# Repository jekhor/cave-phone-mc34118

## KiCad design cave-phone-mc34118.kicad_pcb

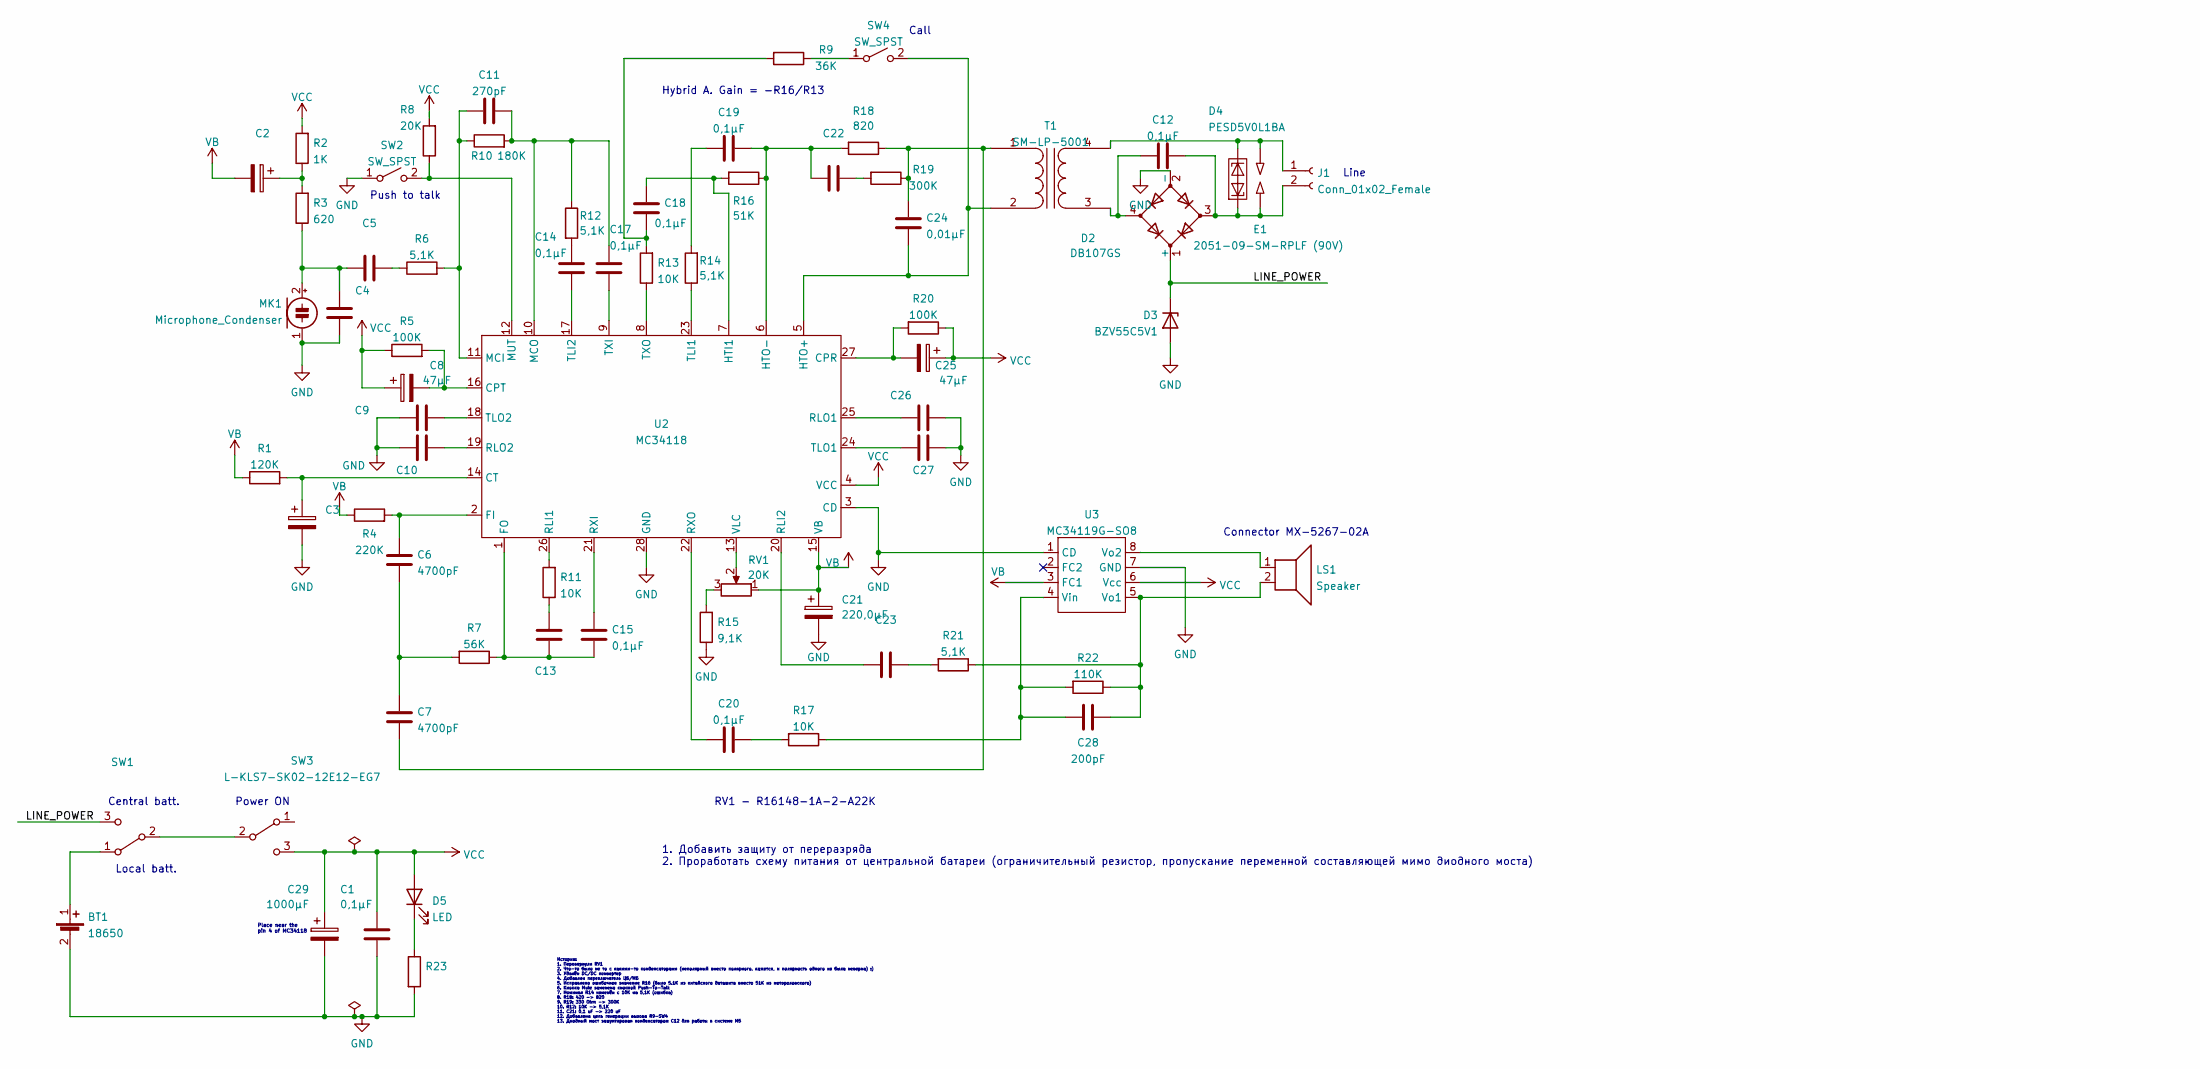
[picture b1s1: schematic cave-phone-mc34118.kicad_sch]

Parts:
BT1: 18650; BatteryHolder_MPD_BH-18650-PC2
C1, C12, C14, C15, C17, C18, C19, C20: 0,1µF; C_0805_2012Metric_Pad1.18x1.45mm_HandSolder
C2, C3: (no value)
C4, C5, C9, C10, C13, C22, C23, C26, C27: C_0805_2012Metric_Pad1.18x1.45mm_HandSolder
C6, C7: 4700pF; C_0805_2012Metric_Pad1.18x1.45mm_HandSolder
C8: 47µF; CP_EIA-3528-21_Kemet-B_Pad1.50x2.35mm_HandSolder
C11: 270pF; C_0805_2012Metric_Pad1.18x1.45mm_HandSolder
C21: 220,0µF
C24: 0,01µF; C_0805_2012Metric_Pad1.18x1.45mm_HandSolder
C25: 47µF
C28: 200pF; C_0805_2012Metric_Pad1.18x1.45mm_HandSolder
C29: 1000µF
D2: DB107GS; Diode_Bridge_Vishay_DFS
D3: BZV55C5V1; D_MiniMELF
D4: PESD5V0L1BA; D_SOD-323
D5: LED; LED_D3.0mm
E1: 2051-09-SM-RPLF (90V); Fuse_1812_4532Metric
J1: Conn_01x02_Female
LS1: Speaker; Molex_SPOX_5267-02A_1x02_P2.50mm_Vertical
MK1: Microphone_Condenser; MIC_CMA-4544PF-W
R1: 120K
R2: 1K
R3: 620
R4: 220K
R5, R20: 100K
R6, R12, R14, R21: 5,1K
R7: 56K
R8: 20K
R9: 36K
R10: 180K
R11, R13, R17: 10K
R15: 9,1K
R16: 51K
R18: 820
R19: 300K
R22: 110K
R23: (no value)
RV1: 20K; Potentiometer_Alps_RK163_Single_Horizontal
SW1: KLS7-SK02-12E12
SW2, SW4: SW_SPST
SW3: L-KLS7-SK02-12E12-EG7; KLS7-SK02-12E12
T1: SM-LP-5001
U2: MC34118; SOIC-28W_7.5x17.9mm_P1.27mm
U3: MC34119G-SO8; SOP-8_3.9x4.9mm_P1.27mm

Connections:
/LINE_POWER: D2.1 (+), D3.1 (K), SW1.3 (C)
GND: BT1.2 (-), C1.2, C3.2, C4.1, C9.1, C10.1, C21.2, C26.1, C27.1, C29.2, D2.2 (-), D3.2 (A), MK1.1 (-), R15.1, R23.2, SW2.1 (A), U2.3 (CD), U2.28 (GND), U3.1 (CD), U3.7 (GND)
unnamed: BT1.1 (+), SW1.1 (A)
unnamed: C2.1, R2.1, R3.2
unnamed: C3.1, R1.2, U2.14 (CT)
unnamed: C4.2, C5.1, MK1.2 (+), R3.1
unnamed: C5.2, R6.1
unnamed: C6.1, C7.2, R7.2
unnamed: C6.2, R4.2, U2.2 (FI)
unnamed: C8.2, R5.2, U2.16 (CPT)
unnamed: C9.2, U2.18 (TLO2)
unnamed: C10.2, U2.19 (RLO2)
unnamed: C11.1, C17.2, R10.2, R12.1, U2.10 (MCO)
unnamed: C11.2, R6.2, R10.1, U2.11 (MCI)
unnamed: C12.1, D2.3, D4.1 (K1), E1.1, J1.2
unnamed: C12.2, D2.4, T1.3 (SA)
unnamed: C13.1, C15.1, R7.1, U2.1 (FO)
unnamed: C13.2, R11.1
unnamed: C14.1, U2.17 (TLI2)
unnamed: C14.2, R12.2
unnamed: C15.2, U2.21 (RXI)
unnamed: C17.1, U2.9 (TXI)
unnamed: C18.1, R9.2, R13.2
unnamed: C18.2, R16.2, U2.7 (HTI1)
unnamed: C19.1, C22.2, R16.1, R18.2, U2.6 (HTO-)
unnamed: C19.2, R14.2
unnamed: C20.1, R17.2
unnamed: C20.2, U2.22 (RXO)
unnamed: C22.1, R19.2
unnamed: C23.1, R21.2
unnamed: C23.2, U2.20 (RLI2)
unnamed: C7.1, C24.1, R18.1, R19.1, T1.1 (AA)
unnamed: C24.2, SW4.2 (B), T1.2 (AB), U2.5 (HTO+)
unnamed: C25.2, R20.2, U2.27 (CPR)
unnamed: C26.2, U2.25 (RLO1)
unnamed: C27.2, U2.24 (TLO1)
unnamed: C28.1, LS1.2, R21.1, R22.1, U3.5 (Vo1)
unnamed: C28.2, R17.1, R22.2, U3.4 (Vin)
unnamed: D4.2 (A), E1.2, J1.1, T1.4 (SB)
unnamed: D5.1 (K), R23.1
unnamed: LS1.1, U3.8 (Vo2)
unnamed: R8.1, SW2.2 (B), U2.12 (MUT)
unnamed: R9.1, SW4.1 (A)
unnamed: R11.2, U2.26 (RLI1)
unnamed: R13.1, U2.8 (TXO)
unnamed: R14.1, U2.23 (TLI1)
unnamed: R15.2, RV1.3
unnamed: RV1.2, U2.13 (VLC)
unnamed: SW1.2 (B), SW3.2 (B)
VB: C2.2, C21.1, R1.1, R4.1, RV1.1, U2.15 (VB), U3.3 (FC1)
VCC: C1.1, C8.1, C25.1, C29.1, D5.2 (A), R2.2, R5.1, R8.2, R20.1, SW3.3 (C), U2.4 (VCC), U3.6 (Vcc)

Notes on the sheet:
Connector MX-5267-02A
Central batt.
1. Добавить защиту от переразряда 2. Проработать схему питания от центральной батареи (ограничительный резистор, пропускание переменной составляющей мимо диодного моста)
Hybrid A. Gain = -R16/R13
Call
Push to talk
Place near the pin 4 of MC34118
Power ON
История: 1. Перевернули RV1 2. Что-то было не то с какими-то конденсаторами (неполярный вместо полярного, кажется, и полярность одного из была неверна) :) 3. Удалён DC/DC конвертер 4. Добавлен переключатель ЦБ/МБ 5. Исправлено ошибочное значение R16 (было 5.1К из китайского даташита вместо 51К из м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
RV1 - R16148-1A-2-A22K
Line
Local batt.

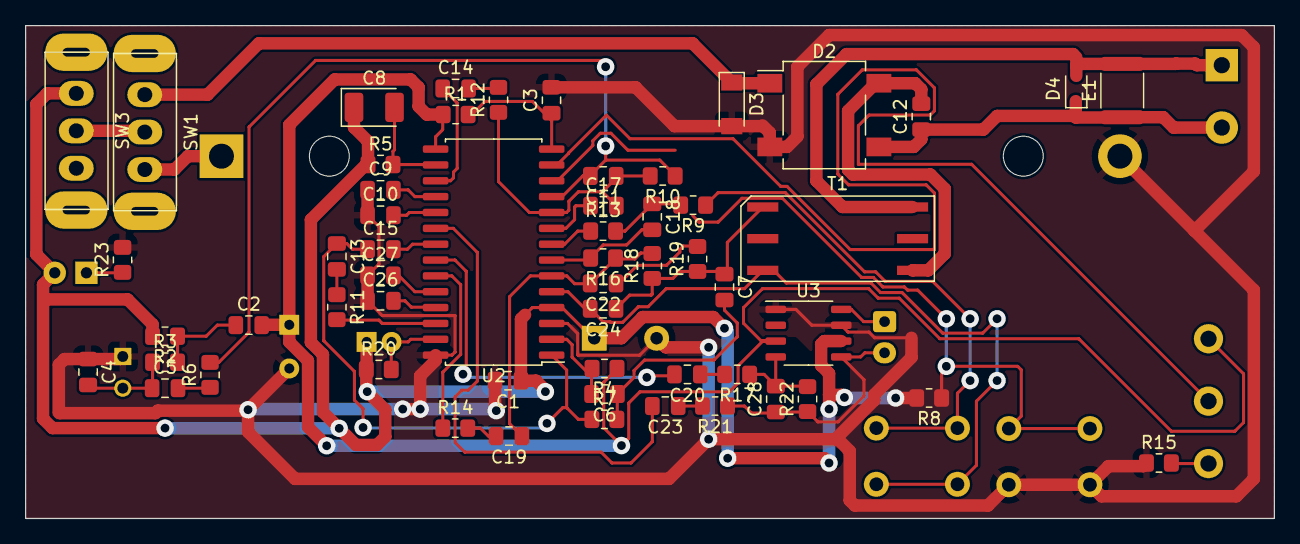
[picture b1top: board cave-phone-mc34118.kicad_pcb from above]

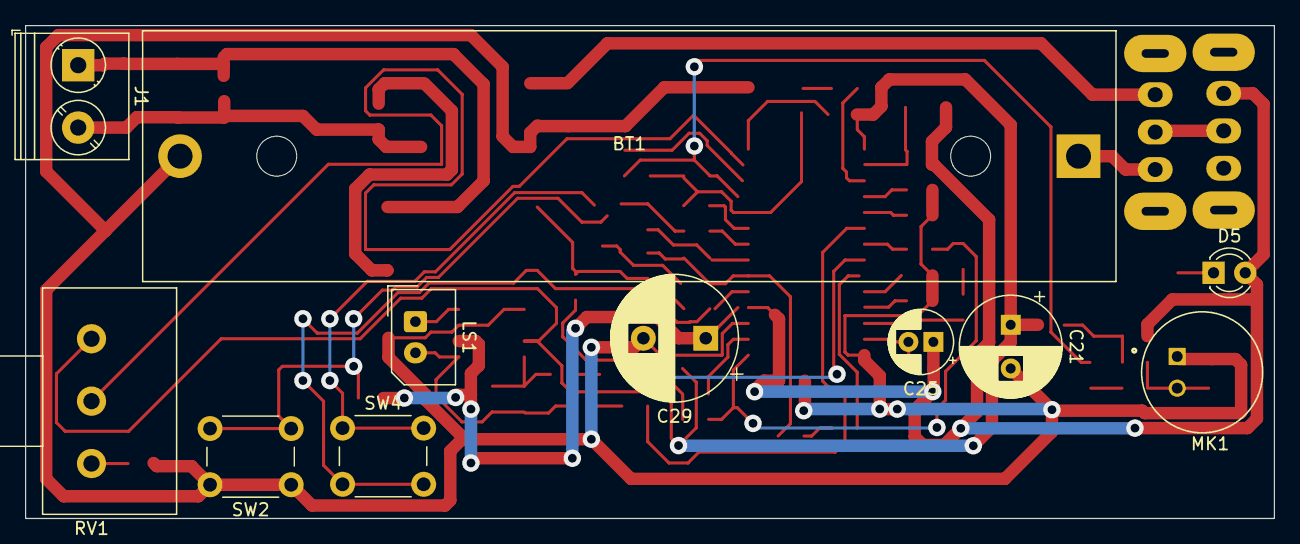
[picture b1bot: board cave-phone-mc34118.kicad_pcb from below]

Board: 2 copper layers, 100.1 x 39.5 mm, 68 parts (11 on the bottom side), 51 nets.

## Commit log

2022-02-20 Reference schematics (from the datasheet)
2022-02-26 v0.1 (wrong U2 package)
2022-02-28 Rework PCB for right MC34118 package
2022-03-22 Fix prototype status
2022-04-25 sch: Remove DC-DC
2022-04-26 Fix some errors and add improvements
2022-04-26 WiP: New PCB (0805 SMDs)
2022-04-27 WiP: New PCB
